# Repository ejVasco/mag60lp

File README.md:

# mag60lp
WIP 60&amp; low profile keyboard with the goal of easy compact storage hopefully via some magnetic attachment system. 

## Progress Report:
| |Task | Status | Notes |
|-|-|-|-
|Designing| Layout | Researching | 60% Split
| | PCB | In Progress | Split 
| | Plate | Researching | 
| | Case | Not started | seems simple enough except for the magnetic mechanism I want
| | Plate and PCB mounting mechanism | Not Started | Gasket seems really popular nowadays
| | Bill of parts | Not Started | screws, heat inserted standoffs, magnets, diodes, microcontrollers, trrs connectors, etc.
| Choose | Switches | Not Started | Low Profile Kailh Choc V2 Switches
| | Plate Material | Not Started | Want Quiet
| | Case Material | Not Started | Want Quiet and possible transparent
| | Case Foam | Not Started | Optional, but not if transparent case
| | Microcontroller | Researching | Between Pro Micro and Elite C
| | Other hardware (TRRS, CapsLock LED, possible OLED screen, diodes) | Not Started | Connect the two halves
| | Stabilizers | Not Started | ... do low profile have stabs?
| | Keycaps | Not Started | Is it possible to get stepped capslock? also want something uniform or blank so I don't have to look at qwerty and also so I only have a single height to think about while designing the case closing mechanism, better be some nice double shot if it has legends on it.
| | Button for reset switch for flashing firmware easier | Not Started | Just to make it easier if anyone actually builds this.
| | Cables | Not Started | Keep in mind cable length and maybe color match or something.
| Assemble | Lube switches | Not Started | ... can you lube low profile switches?
| | Diodes on PCB | Not Started | probably test too
| | put more soldering tasks here later
| | Heat inserted threads/standoffs for the case | Not Started
| Program | Basic Firmware | Not Started | lowkey scared
| | Via Compatability | Not Started | Desperately want
# Cache refresh

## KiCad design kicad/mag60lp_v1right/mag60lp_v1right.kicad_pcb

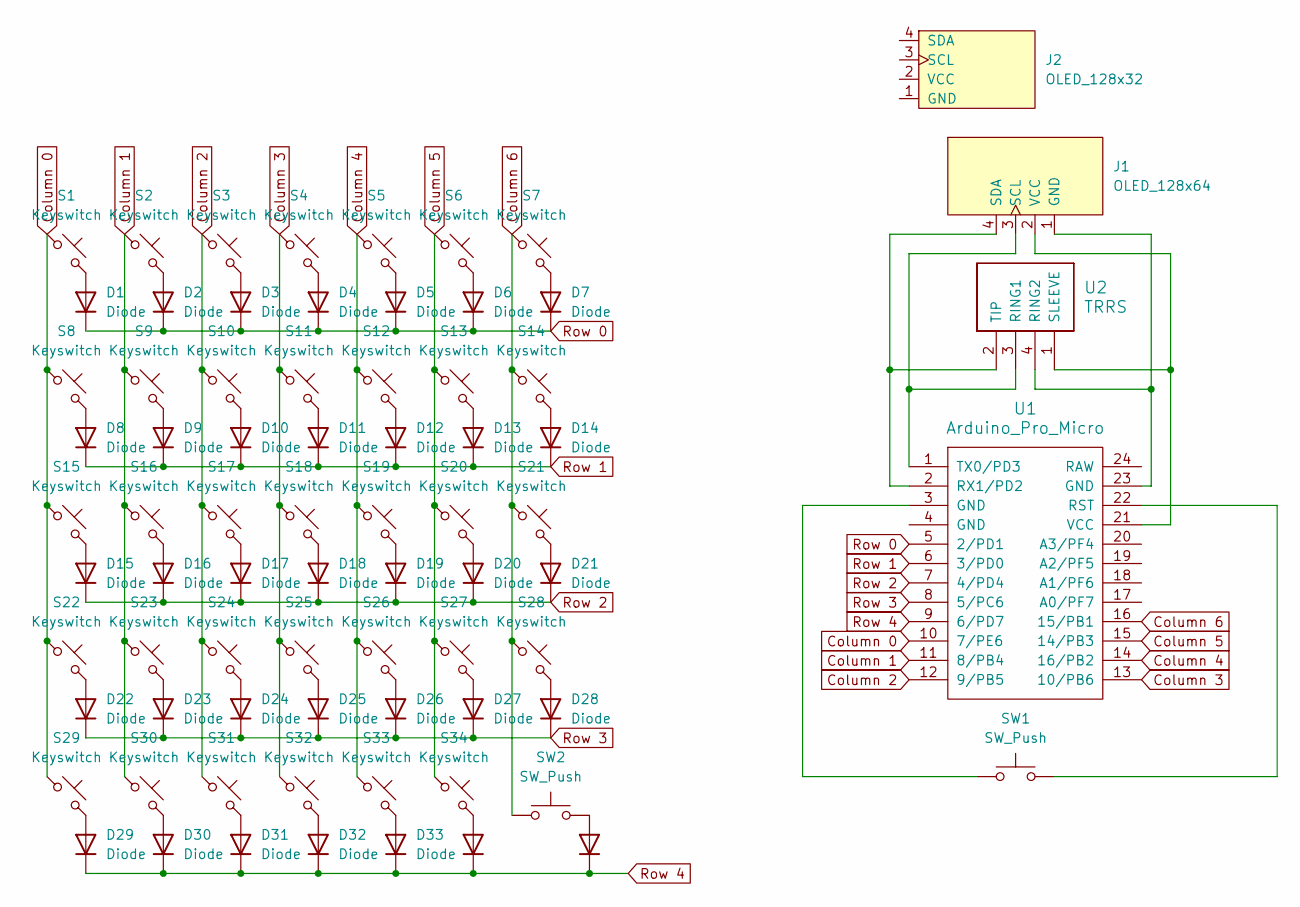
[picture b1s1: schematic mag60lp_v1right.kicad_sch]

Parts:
D1, D2, D3, D4, D5, D6, D7, D8, D9, D10, D11, D12, D13, D14, D15, D16, D17, D18, D19, D20, D21, D22, D23, D24, D25, D26, D27, D28, D29, D30, D31, D32, D33, D34, D35: Diode; Diode_DO-35
J1: OLED_128x64
J2: OLED_128x32
S1, S2, S3, S4, S5, S6, S7, S8, S9, S10, S11, S12, S13, S14, S15, S16, S17, S18, S19, S20, S22, S23, S24, S25, S26: Keyswitch; Choc_V1V2_1.00u
S21: Keyswitch; Choc_V1V2_2.00u
S27, S29: Keyswitch; Choc_V1V2_2.75u
S28: Keyswitch; Choc_V1V2_1.50u
S30, S31, S32, S33, S34: Keyswitch; Choc_V1V2_1.25u
SW1, SW2: SW_Push; SW_PUSH_6mm_H4.3mm
U1: Arduino_Pro_Micro
U2: TRRS; TRRS_PJ-320A

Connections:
Column 0: S1.1, S8.1, S15.1, S22.1, S29.1, U1.10 (7/PE6)
Column 1: S2.1, S9.1, S16.1, S23.1, S30.1, U1.11 (8/PB4)
Column 2: S3.1, S10.1, S17.1, S24.1, S31.1, U1.12 (9/PB5)
Column 3: S4.1, S11.1, S18.1, S25.1, S32.1, U1.13 (10/PB6)
Column 4: S5.1, S12.1, S19.1, S26.1, S33.1, U1.14 (16/PB2)
Column 5: S6.1, S13.1, S20.1, S27.1, S34.1, U1.15 (14/PB3)
Column 6: S7.1, S14.1, S21.1, S28.1, SW2.1, U1.16 (15/PB1)
unnamed: D1.2 (A), S1.2
unnamed: D2.2 (A), S2.2
unnamed: D3.2 (A), S3.2
unnamed: D4.2 (A), S4.2
unnamed: D5.2 (A), S5.2
unnamed: D6.2 (A), S6.2
unnamed: D7.2 (A), S7.2
unnamed: D8.2 (A), S8.2
unnamed: D9.2 (A), S9.2
unnamed: D10.2 (A), S10.2
unnamed: D11.2 (A), S11.2
unnamed: D12.2 (A), S12.2
unnamed: D13.2 (A), S13.2
unnamed: D14.2 (A), S14.2
unnamed: D15.2 (A), S15.2
unnamed: D16.2 (A), S16.2
unnamed: D17.2 (A), S17.2
unnamed: D18.2 (A), S18.2
unnamed: D19.2 (A), S19.2
unnamed: D20.2 (A), S20.2
unnamed: D21.2 (A), S21.2
unnamed: D22.2 (A), S22.2
unnamed: D23.2 (A), S23.2
unnamed: D24.2 (A), S24.2
unnamed: D25.2 (A), S25.2
unnamed: D26.2 (A), S26.2
unnamed: D27.2 (A), S27.2
unnamed: D28.2 (A), S28.2
unnamed: D29.2 (A), S29.2
unnamed: D30.2 (A), S30.2
unnamed: D31.2 (A), S31.2
unnamed: D32.2 (A), S32.2
unnamed: D33.2 (A), S33.2
unnamed: D34.2 (A), S34.2
unnamed: D35.2 (A), SW2.2
unnamed: J1.1 (GND), U1.23 (GND), U2.4 (RING2)
unnamed: J1.3 (SCL), U1.1 (TX0/PD3), U2.3 (RING1)
unnamed: J1.4 (SDA), U1.2 (RX1/PD2), U2.2 (TIP)
unnamed: J1.2 (VCC), U1.21 (VCC), U2.1 (SLEEVE)
unnamed: SW1.1, U1.3 (GND)
unnamed: SW1.2, U1.22 (RST)
Row 0: D1.1 (K), D2.1 (K), D3.1 (K), D4.1 (K), D5.1 (K), D6.1 (K), D7.1 (K), U1.5 (2/PD1)
Row 1: D8.1 (K), D9.1 (K), D10.1 (K), D11.1 (K), D12.1 (K), D13.1 (K), D14.1 (K), U1.6 (3/PD0)
Row 2: D15.1 (K), D16.1 (K), D17.1 (K), D18.1 (K), D19.1 (K), D20.1 (K), D21.1 (K), U1.7 (4/PD4)
Row 3: D22.1 (K), D23.1 (K), D24.1 (K), D25.1 (K), D26.1 (K), D27.1 (K), D28.1 (K), U1.8 (5/PC6)
Row 4: D29.1 (K), D30.1 (K), D31.1 (K), D32.1 (K), D33.1 (K), D34.1 (K), D35.1 (K), U1.9 (6/PD7)

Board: 2 copper layers, 75 parts (35 on the bottom side), 53 nets, no tracks yet.

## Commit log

2025-03-01 re-uped the repo
2025-03-01 Trigger GitHub contributor refresh
2025-03-01 Trigger GitHub contributor refresh again
2025-03-01 worked on pcb designs
2025-03-01 deleted uneccesary kicad file
2025-03-01 attempt to ignore backup for kicad
2025-03-01 updated pcb design status to in progress
2025-03-02 learned about choc v1 vs v2
2025-03-02 worked on cpb, but im still so confused
2025-03-02 pausing design untill i can figure out which switches for certain i want to use
    see
    #### Mar02.2025 Update for details
2025-03-03 halfway through pcb
2025-03-03 pcb done?
    i cant rember rn, i did this last night
2025-03-04 finalized switches to try
2025-03-04 added parts list as a seperate file
2025-03-04 small edit
2025-03-05 im losing my mind working on this
2025-03-05 layout im going for added temporarily
2025-03-05 added basic config.yaml for the left half
